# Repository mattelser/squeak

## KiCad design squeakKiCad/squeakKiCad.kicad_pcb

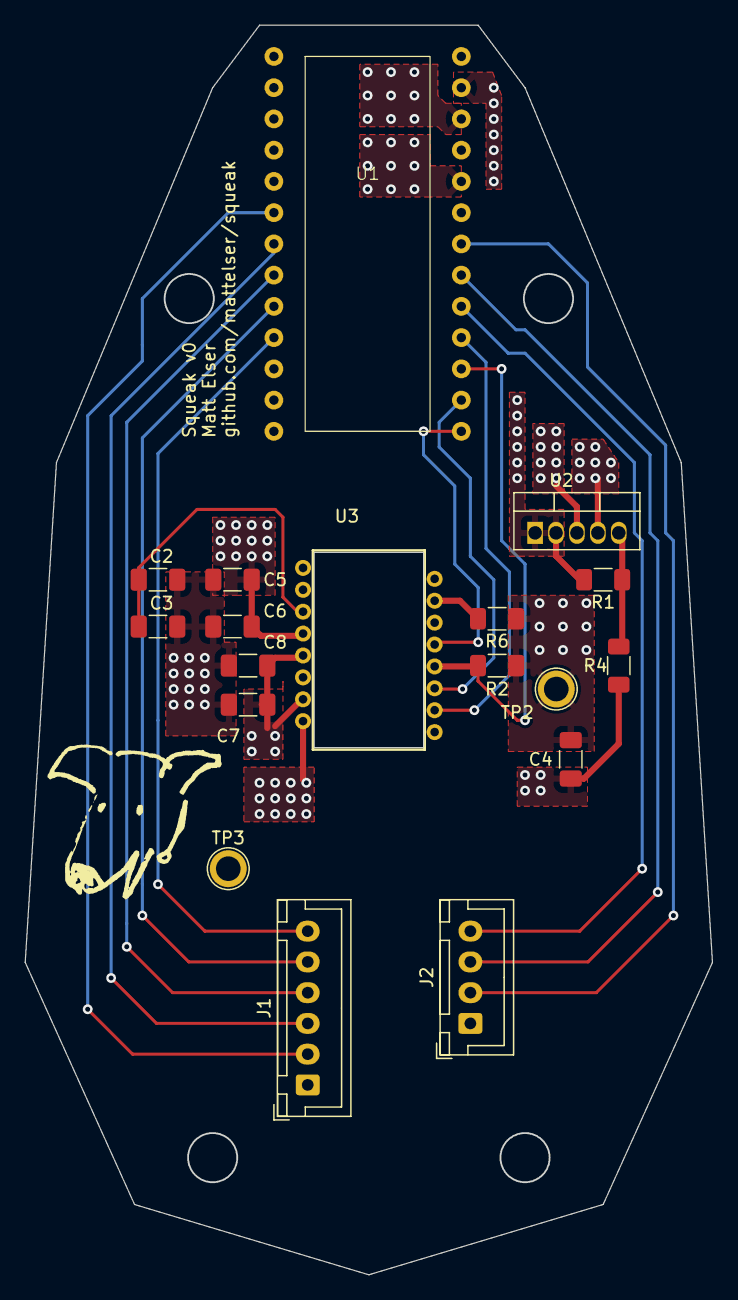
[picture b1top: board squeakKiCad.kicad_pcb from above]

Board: 4 copper layers, 55.9 x 101.6 mm, 18 parts (0 on the bottom side), 19 nets.

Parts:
C2: 4.7uF; C_1206_3216Metric_Pad1.33x1.80mm_HandSolder
C3, C6, C8: 0.1uF; C_1206_3216Metric_Pad1.33x1.80mm_HandSolder
C4: 33uF; C_1206_3216Metric_Pad1.33x1.80mm_HandSolder
C5, C7: 10uF; C_1206_3216Metric_Pad1.33x1.80mm_HandSolder
J1: Conn_01x06_Pin; JST_XH_B6B-XH-A_1x06_P2.50mm_Vertical
J2: Conn_01x04_Pin; JST_XH_B4B-XH-A_1x04_P2.50mm_Vertical
R1: 47k; R_1206_3216Metric_Pad1.30x1.75mm_HandSolder
R2: 10k; R_1206_3216Metric_Pad1.30x1.75mm_HandSolder
R4: 100k; R_1206_3216Metric_Pad1.30x1.75mm_HandSolder
R6: 10 Ohm; R_1206_3216Metric_Pad1.30x1.75mm_HandSolder
TP2, TP3: TestPoint; TestPoint_Plated_Hole_D2.0mm
U1: KB2040
U2: BA00JC5WT; TO-220-5_Vertical
U3: PMW3360DM-T2QU; PMW3360

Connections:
1.9V: C4.1, C5.1, C6.1, R2.2, R6.1, TP2.1, U2.4 (OUT), U3.4 (VDD)
3.3V: C7.1, C8.1, TP3.1, U1.22 (3.3V), U3.5 (VDDIO), U3.7 (~RESET)
5V: R1.2, U1.25 (RAW), U2.1 (Ctl), U2.2 (Vcc)
GND: C2.2, C3.2, C4.2, C5.2, C6.2, C7.2, C8.2, J1.1, J2.1, R4.1, U1.4 (Gnd), U1.5 (Gnd), U1.24 (GND), U2.3 (Gnd), U3.8 (GND)
unnamed: J1.2, U1.6 (D2)
unnamed: J1.3, U1.7 (D3)
unnamed: J1.4, U1.8 (D4)
unnamed: J1.5, U1.9 (D5)
unnamed: J1.6, U1.10 (D6)
unnamed: J2.2, U1.20 (A2)
unnamed: J2.3, U1.19 (A1)
unnamed: J2.4, U1.18 (A0)
unnamed: U1.14 (D10/CS), U3.13 (~CS)
unnamed: R2.1, U1.16 (DIN), U3.12 (DOUT)
unnamed: U1.15 (DOUT), U3.11 (DIN)
unnamed: U1.17 (SCK), U3.10 (SCLK)
unnamed: R1.1, R4.2, U2.5 (Adj)
unnamed: R6.2, U3.15 (LED_P)
unnamed: C2.1, C3.1, U3.3 (VDDPIX)

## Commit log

2023-10-07 initial commit - bread board mouse working
2023-11-26 derived from QMK, copying left
2024-01-15 Added v0 circuit in kicad
2024-01-23 add jst connector to schematic
2024-12-29 add draft of printable shell
2024-12-31 revised schematic: sensor pins at wrong voltage
